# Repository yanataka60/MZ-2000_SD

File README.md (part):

# MZ-80B、MZ-2000、MZ-2200にSD-CARDからのアプリケーション起動、ロード、セーブ機能

　MZ-80B、MZ-2000、MZ-2200でSD-CARDからのアプリケーション起動、BASICなどのアプリケーションからSD-CARDへのロード、セーブを実現するものです。

　MZ-80B、MZ-2000、MZ-2200では「/」キーを押しながら電源を入れる、又は「/」キーを押しながらIPLボタンを押すことでI/Oデバイスとして繋いだROMからプログラムを読み込ませて起動する機能があります。

　この機能を使ってSD-CARDからアプリケーションを起動させる機能を持たせたMONITOR SB-1520(MZ-80B)、MONITOR 1Z-1Z001M(MZ-2000)をROM起動させます。

　SD対応MONITORからはFD又はFDLコマンドでSDからアプリケーションをLOAD実行ができます。

　LOAD実行範囲は、0000h～F7FFhです。アプリケーション、ゲームを起動させるにはほぼ問題ないと思います。

　(2023.1.1)FDコマンドでの読み込み実行で読み込み終了アドレスがF800h以降であっても読み込みスタートアドレスが12A0h以降だった場合に限りFFFFhまでの読み込みに対応しました。

　なお、アプリケーション中でのSD-CARDとのロード、セーブについては、アプリケーションごとにSD-CARD対応化を行う必要があります。

　EXPANSION UNITが接続されていないMZ-2000、MZ-2200でも使えます。

　MZ-2500の80Bモード、2000モードでも使えます。

#### (追記2023.3.8)MZ-2500のZ80PIOとI/Oアドレスがぶつかっていることを失念していました。80Bモード、2000モードでは問題ありませんが、MZ-2500モードではMZ-2000_SDを接続したままRS-232C、マウスは使えません。

　現在、アプリケーション中でのSD-CARDとのLOAD、SAVEに対応できているものは以下のとおりです。

### MZ-2000、MZ-2200用
|アプリケーション名|備考|
| ------------ | ------------ |
|BASIC MZ-1Z001||
|BASIC MZ-1Z002||
|16BIT BASIC 1Z-012||
|MZ-LOGO V1.0||
|MZ-LISP       |I/O '85/3月号|
|S-OS SWORD TAPE版|Oh!MZ '86/2月号|
|TS-2000       |I/O '82/12月号|
|BASE          |I/O '83/1月号|
|WICS          |I/O '83/2月号|
|EDASM         |Oh!MZ '85/1月号|
|TTL           |Oh!MZ '84/10月号|

### MZ-80B用
|アプリケーション名|備考|
| ------------ | ------------ |
|BASIC SB-5520 ||
|MZ-LISP       |I/O '85/3月号|
|FORTRAN       |I/O別冊MZ-80B活用研究|
|S-OS SWORD TAPE版|Oh!MZ '86/2月号|
|TS-1000       |I/O '82/2月号 I/O別冊MZ-80B活用研究|
|WICS          |I/O '82/3月号 I/O別冊MZ-80B活用研究|
|TTL           |Oh!MZ '84/10月号|

　なお、Arduino、ROMへ書き込むための機器が別途必要となります。

## 回路図
　2枚構成のRev2.3(Rev3.3)と1枚構成のRev4.3があります。

　Rev2.3(Rev3.3)は手元にSD-CARDが置ける、拡張ボックスが無くてもMZ-2000に装着が可能です。

　Rev4.3は拡張ボックス専用でSD-CARDが背面にいってしまいますが、すっきりと収納できます。

　好きな方を選択してください。

　注1)MZ-2000_SD(SD-CARD UNIT基板)でU5 GAL22V10をTTLに置き換えたRev3.3基板のKiCadデータを追加しました。後述「MZ-2000_SD(SD-CARD UNIT基板)Rev3.3」を参照してください。

　注2)MZ-80Bに拡張I/Oポートが装備されていない場合の接続方法については後述「MZ-80Bの拡張I/Oポートを使わずに接続する場合」を参照してください。

　KiCadフォルダ内のMZ-2000_EXT-BOARDフォルダのMZ-2000_EXT-BOARD.pdf、MZ2000_SDフォルダのMZ2000_SD.pdfを参照してください。

[インタフェース基板回路図](https://github.com/yanataka60/MZ-2000_SD/blob/main/KiCad/MZ-2000_EXT-BOARD/MZ-2000_EXT-BOARD.pdf)

[SD-CARD UNIT Rev2.3基板回路図](https://github.com/yanataka60/MZ-2000_SD/blob/main/KiCad/MZ-2000_SD/MZ2000_SD.pdf)

## 部品

### MZ-2000_EXT-BOARD(インタフェース基板)
|番号|品名|数量|備考|
| ------------ | ------------ | ------------ | ------------ |
|J2|2x22Pinコネクタ|1|秋月電子通商 PH-2x40SGなど|
|J4|DCジャック|1|秋月電子通商 MJ-179PHなど|
|J5|2x22Pinコネクタ|1|秋月電子通商 PH-2x40RGなど(EXPANSION UNITを使う場合には必要ありません)|
|S1|3Pスライドスイッチ|1|秋月電子通商 SS12D01G4など|

### MZ-2000_SD(SD-CARD UNIT基板)Rev2.3
|番号|品名|数量|備考|
| ------------ | ------------ | ------------ | ------------ |
|J1|2x22Pinコネクタ|1|秋月電子通商 PH-2x40RGなど|
||J2、J3のいずれか|||
|J2|Micro_SD_Card_Kit|1|秋月電子通商 AE-microSD-LLCNV (注1)|
|J3|MicroSD Card Adapter|1|Arduino等に使われる5V電源に対応したもの (注3)|
|U1,U2|74LS273|2||
|U3|8255|1||
|U4|Arduino_Pro_Mini_5V|1|Atmega328版を使用 168版は不可。(注2)|
|U5|GAL22V10|1||
|U6|27256/29C256/27512/27C512相当品|1|27256/29C256を使うときは、S1を5V側にして使うこと。28C256はピン配置が違うので使えません。|
|U9|74LS245|1||
|C1|電解コンデンサ 16v100uF|1||
|C2-C7|積層セラミックコンデンサ 0.1uF|6||
|S1|3Pスライドスイッチ|1|秋月電子通商 SS12D01G4など|
||ピンヘッダ|2Pin分|Arduino_Pro_MiniにはA4、A5用のピンヘッダが付いていないため別途調達が必要です 秋月電子通商 PH-1x40SGなど|
||ピンソケット(任意)|26Pin分|Arduino_Pro_Miniを取り外し可能としたい場合に調達します 秋月電子通商 FHU-1x42SGなど|

　　　注1)秋月電子通商　AE-microSD-LLCNVのJ1ジャンパはショートしてください。

　　　注2)Arduino Pro MiniはA4、A5ピンも使っています。

　　　注3)Arduino等に使われる5V電源に対応したMicroSD Card Adapterも正しく信号を繋げば使えるとご報告いただきました。

### MZ-2000_SD(SD-CARD UNIT基板)Rev3.3
　MZ-2000_SD(SD-CARD UNIT基板)Rev2.3のU5 GAL22V10が以下の部品に置き換わっています。以下の部品以外はMZ-2000_SD(SD-CARD UNIT基板)Rev2.3の説明を参照してください。
|番号|品名|数量|備考|
| ------------ | ------------ | ------------ | ------------ |
|U5 U7|74LS04|2||
|U8 U11|74LS30|2||
|U10|74LS10|1||
|C8-C11|積層セラミックコンデンサ 0.1uF|4||

#### Rev3.3回路図
[SD-CARD UNIT基板Rev3.3回路図](https://github.com/yanataka60/MZ-2000_SD/blob/main/KiCad/MZ-2000_SD_3_3/MZ2000_SD_33.pdf)

### MZ-2000_SD(SD-CARD UNIT基板)Rev4.3
　EXT-BOARDとSD-CARD UNIT基板Rev3.3を1枚の基板とした拡張スロット装着専用の基板となります。

　MZ-2000、MZ-2200ならEXPANSION UNIT、MZ-80Bなら拡張I/Oポート、MZ-2500なら拡張ユニットが必要です。

　MZ-2000_SD(SD-CARD UNIT基板)Rev2.3のU5 GAL22V10がTTLに置き換わっています。

　また、J1はカードエッジになっていますので「2x22Pinコネクタ」は必要なく、EXT-BOARDを必要としないのでフラットケーブルも不要です。

|番号|品名|数量|備考|
| ------------ | ------------ | ------------ | ------------ |
||J5、J6のいずれか|||
|J5|Micro_SD_Card_Kit|1|秋月電子通商 AE-microSD-LLCNV (注1)|
|J6|MicroSD Card Adapter|1|Arduino等に使われる5V電源に対応したもの (注3)|
|U1,U2|74LS04|2||
|U3,U4|74LS30|2||
|U5|74LS10|1||
|U6,U7|74LS273|2||
|U8|74LS245|1||
|U9|27256/29C256/27512/27C512相当品|1|27256/29C256を使うときは、S1を5V側にして使うこと。28C256はピン配置が違うので使えません。|
|U10|8255|1||
|U11|Arduino_Pro_Mini_5V|1|Atmega328版を使用 168版は不可。(注2)|
|C1|電解コンデンサ 16v100uF|1||
|C2-C11|積層セラミックコンデンサ 0.1uF|10||
|S2|3Pスライドスイッチ|1|秋月電子通商 SS12D01G4など|
||ピンヘッダ|2Pin分|Arduino_Pro_MiniにはA4、A5用のピンヘッダが付いていないため別途調達が必要です 秋月電子通商 PH-1x40SGなど|
||ピンソケット(任意)|26Pin分|Arduino_Pro_Miniを取り外し可能としたい場合に調達します 秋月電子通商 FHU-1x42SGなど|

　　　注1)秋月電子通商　AE-microSD-LLCNVのJ1ジャンパはショートしてください。

　　　注2)Arduino Pro MiniはA4、A5ピンも使っています。

　　　注3)Arduino等に使われる5V電源に対応したMicroSD Card Adapterも正しく信号を繋げば使えるとご報告いただきました。

#### Rev4.3回路図
[SD-CARD UNIT基板Rev4.3回路図](https://github.com/yanataka60/MZ-2000_SD/blob/main/KiCad/MZ-2000_SD_4_3/MZ2000_SD_43.pdf)

.JPG)
.JPG)
.JPG)

### MicroSD Card Adapterを使う
J3に取り付けます。

MicroSD Card Adapterについているピンヘッダを除去してハンダ付けするのが一番確実ですが、J3の穴にMicroSD Card Adapterをぴったりと押しつけ、裏から多めにハンダを流し込むことでハンダ付けをする方法もあります。なお、この方法の時にはしっかりハンダ付けが出来たかテスターで導通を確認しておいた方が安心です。

ハンダ付けに自信のない方はJ2の秋月電子通商　AE-microSD-LLCNVをお使いください。AE-microSD-LLCNVならパワーLED、アクセスLEDが付いています。

.JPG)

.JPG)

.JPG)

.JPG)

### その他必要なもの
　基板のコネクタは2x22Pinで設計していますが、2.54mmピッチ2x22Pinフラットケーブルが手に入りにくいので2.54mmピッチ2x25Pinフラットケーブルで代用しています。

　2.54mmピッチ2x22Pinフラットケーブルが手に入るようであればそちらをお使いください。

#### EXPANSION UNITの拡張スロットに挿入して使用する場合
・2.54mmピッチ2x25Pinフラットケーブル

　長さは50～70cmあれば前面まで持ってこられます。

#### EXPANSION UNITを使わない場合
・2.54mmピッチ2x25Pinフラットケーブル、ただし片側はカードエッジコネクタ

　長さは50～70cmあれば全面まで持ってこられます。

・2.54mmピッチ2x25Pinフラットケーブル

　インタフェース基板とSD-CARD UNIT基板は重ねられるので10cm以上の長さがあれば十分です。

## GAL22V10への書込み
　WINCUPLファルダのMZ2000_SD.jedをROMライター(TL866II Plus等)を使ってGAL22V10に書き込んでください。

## ROMへの書込み
　まず、BASICからMONITOR(0000h～129Fh)を抜き出し、バイナリファイルとして保存します。

|機種名|BASIC名|モニタ名|
| ------------ | ------------ | ------------ |
|MZ-80B|SB-5520|SB-1520|
|MZ-2000、MZ-2200|MZ-1Z001 or MZ-1Z002|MZ-1Z001M|

バイナリエディタで以下の修正をします。
### MZ-80B SB-1520
|ADDRESS|修正前|修正後|
| ------------ | ------------ | ------------ |
|0000|C3 3B 00|00 18 38|
|00AE|01 76 49(C3 76 49)|C3 A0 12|
|00F6|56 17 02|46 00 F8|
|0252|16 01 21|C3 03 F8|
|0283|16 02 ED|C3 06 F8|
|028F|16 04 21|C3 09 F8|
|02B3|16 08 ED|C3 0C F8|
|02BF|16 08 ED|C3 0F F8|

### MZ-2000、MZ-2200 MZ-1Z001M
|ADDRESS|修正前|修正後|
| ------------ | ------------ | ------------ |
|0000|C3 3B 00|00 18 38|
|00AE|01 05 4C(C3 05 4C)|C3 A0 12|
|00E5|56      |46      |
|00E7|17 02   |00 F8   |
|0252|16 01 21|C3 03 F8|
|0283|16 02 ED|C3 06 F8|
|028F|16 04 21|C3 09 F8|
|02B3|16 08 ED|C3 0C F8|
|02BF|16 08 ED|C3 0F F8|

　次にEXT-ROMフォルダ内のEXT-ROM_SD MZ-80B.bin又はEXT-ROM_SD MZ-2000.binをMONITORの後ろ(12A0h～)に付け加えて保存します。出来上がるバイナリファイルは0000h～198Ehとなるはずです。

　出来上がったバイナリファイルをROMライター(TL866II Plus等)を使って27C256に書き込んでください。

　27C512を使えば二つのバイナリファイルを切り替えて使うような使い方ができます。このとき、一つのバイナリファイルは32KByte、二つ合わせて64KByteにして書き込んでください。

### 参考)起動プロセス
　1　「/」キーを押しながら電源を入れる、又は「/」キーを押しながらIPLボタンを押す。

　2　EXT-ROMからプログラムが読み込まれ、ノーマル時のメモリマップに切り替わった後、リセットされる。

　3　MINITORが起動し、MZの初期化が行われた後、12A0hにJUMPする。

　4　12A0hからの転送プログラムにより、SDアクセスルーチンをF800h以降に転送する。

　5　MZ-2000_SDの8255を初期化する。

　6　12A0hからの転送プログラムが再度起動しないよう00AEhに01hを書き込む。

　7　コマンドプロンプトに戻る。

　8　FDコマンド又はFDLコマンドによりSD-CARD内アプリケーションのLOAD実行が指示されるとF800hのSDアクセスルーチンにJUMPする。

　9　指定したファイルがSDに存在したらスタックポインタをFFFFhに設定する。

　10　MZTファイルのヘッダ情報にあるLOAD開始アドレスからファイル長分をSD-CARDから読み出しメインメモリに書き込む。

　　　この時、LOAD終了アドレスがF800h以降でLOAD開始アドレスが12A0h以降ならSD-LOADルーチンを1200h～124Fhにコピーし1206hにJUMPしてLOADを実行する。

　11　実行開始アドレスが0000hでないならスタックポインタを1140hに設定する。

　12　実行開始アドレスにJUMPする。

### ROMにBOOT LOADERを書き込む方式の追加
　前述のBASICからMONITORを抜き出してROMに書き込む方式は、自分が所有しているBASICから抜き出してROMに書き込むには問題が無いのですが、書き込み済みROMの配布はSHARPの著作権があるので出来ません。

　そこで「@BOOT-A MZ-2000.bin」、「@BOOT-A MZ-80B.bin」というバイナリファイルをSD-CARDから読み込み起動するプログラムをROMに書き込む方式を追加しました。

　ROMに27256を使えば「@BOOT-A MZ-xxxx.bin」、27512を使えば「@BOOT-A MZ-xxxx.bin」と「@BOOT-B MZ-xxxx.bin」を切り替えて読み込むことができます。

　前述「ROMへの書込み」の手順により修正を加えたMONITORの後ろ(12A0h～)にEXT-ROM_SD MZ-2000.bin又はEXT-ROM_SD MZ-80B.binを付け加えて保存したバイナリファイル(従来ROMに書き込んでいたバイナリファイル)を「@BOOT-A MZ-2000.bin」又は「@BOOT-A MZ-80B.bin」のファイルネームでSD-CARDに保存してください。

　27512を使うのであれば同様にBASICを加工したバイナリファイル(従来ROMに書き込んでいたバイナリファイル)を「@BOOT-B MZ-2000.bin」又は「@BOOT-B MZ-80B.bin」のファイルネームでSD-CARDに保存することでスイッチの切り替えで読み込むことができます。

#### BOOT LOADERをROMに書き込む
　BOOT_LOADERフォルダにある「BOOT_A_LOADER.bin」または「BOOT_AB_LOADER.bin」をROMに書き込みます。

　　27256を使用する場合は「BOOT_A_LOADER.bin」を書き込んでください。

　　27512を使用する場合は「BOOT_AB_LOADER.bin」を書き込んでください。

#### 「@BOOT-A MZ-xxxx.bin」を作成してSD-CARDに保存する
　「ROMへの書込み」を参照してバイナリファイル(従来ROMに書き込んでいたバイナリファイル)を作成します。

　出来上がったファイルの名前は、MZ-2000用なら「@BOOT-A MZ-2000.bin」、MZ-80B用なら「@BOOT-A MZ-80B.bin」としてSD-CARDに保存します。

　起動させた機械がMZ-2000か、MZ-80Bか自動的に判断して「@BOOT-A MZ-2000.bin」、「@BOOT-A MZ-80B.bin」のどちらかを読み込まれます。

#### 「@BOOT-B MZ-xxxx.bin」を作成してSD-CARDに保存する(27512を使用する場合)
　後述の「BASICをEXT-ROMから起動させる」を参照してバイナリファイル(従来ROMに書き込んでいたバイナリファイル)を作成し、出来上がったファイルの名前をMZ-2000用なら「@BOOT-B MZ-2000.bin」、MZ-80B用なら「@BOOT-B MZ-80B.bin」としてSD-CARDに保存します。

　起動させた機械がMZ-2000か、MZ-80Bか自動的に判断して「@BOOT-B MZ-2000.bin」、「@BOOT-B MZ-80B.bin」のどちらかを読み込まれます。

#### Arduinoプログラム
　この機能に対応させるためArduinoプログラムも更新しました。この機能を使いたい場合にはArduinoプログラムも書き込み直してください。

## Arduinoプログラム

　MZ-80K_SDと全く同じものを使用しています。

　MZ-80K_SDでソケットを使用して差込式にしているのであればそのままMZ-2000_SDに差して使えます。

　Arduino IDEを使ってMZ-80Kリポジトリ Arduinoフォルダ内のMZ-80K_SD.inoを書き込みます。

　SdFatライブラリを使用しているのでArduino IDEメニューのライブラリの管理からライブラリマネージャを立ち上げて「SdFat」をインストールしてください。

　「SdFat」で検索すれば見つかります。「SdFat」と「SdFat - Adafruit Fork」が見つかりますが「SdFat」のほうを使っています。

注)Arduinoを基板に直付けしている場合、Arduinoプログラムを書き込むときは、MZ-2000本体とは接続を外し、74LS04を外したうえで書き込んでください。

## 接続
### MZ-80B、MZ-2000、MZ-2200、MZ-2500の拡張スロットに差し込む
　インタフェース基板は、安価に発注するために10cmx10cmで設計しているのでMZ-80B、MZ-2000、MZ-2200の拡張カードとしては寸足らずです。右側をガイドスロットに沿って差し込めるように設計しています。

#### 2025.7.14追記) カードエッジコネクタは規格通りです。左側をガイドスロットに沿って差し込むと違うピンが接触してしまうわけではありません。(左側をガイドスロットに沿って差し込もうとしても差し込めません)

　インタフェース基板からMZ-2000_SDへのフラットケーブルは真ん中のJ2に差してください。

### MZ-2200、MZ-80B、MZ-2500拡張スロットへの抜き差しに苦労する場合
　MZ-2200 EXPANSION UNITにインタフェース基板を挿入しようとしたところ、抜き差しが非常に硬く苦労する個体がありました。

　開発ではMZ-2000 EXPANSION UNITでのスムーズな抜き差しを確認していますが、抜き差しに苦労する場合には画像の部分をほんの少しヤスリ掛け(4～5回)するだけでかなりスムーズになりますのでお試しください。

### MZ-2000、MZ-2200のEXPANSION UNITを使わずに接続する場合
　インタフェース基板のカードエッジ反対側のJ5と本体のカードエッジを接続します。

　インタフェース基板からMZ-2000_SDへのフラットケーブルは真ん中のJ2に差してください。

#### カードエッジコネクタを使う
　変則的ではありますが、インタフェース基板に基板用カードエッジコネクタのピンを曲げて付けてみました。

　カードエッジコネクタを基板にハンダ付けすると上面、下面が逆になってしまいますのでカードエッジコネクタは基板の裏面に付ける必要があります。

　カードエッジコネクタB列のピンは90度曲げることでそのままハンダ付けできますが、A列のピンは空中に浮いてしまいますので手配線する必要があります。

　また、MZ-2000本体のカードエッジに挿す時には、基板を逆さまに挿しますのでフラットケーブルが邪魔になって結構斜めになっています。

　ちょっと強引な付け方になりますので試される方は自己責任でお願いします。

### MZ-80Bの拡張I/Oポートを使わずに接続する場合
　MZ-80Bに拡張I/Oポートが装備されていない場合には、MZ-80B用のインタフェース基板を使用します。

[MZ-80Bインタフェース基板回路図](https://github.com/yanataka60/MZ-2000_SD/blob/main/KiCad/MZ-80B_EXT-BOARD/mz-80b.pdf)

|番号|品名|数量|備考|
| ------------ | ------------ | ------------ | ------------ |
|J2|2x22Pinコネクタ|1|秋月電子通商 PH-2x40SGなど|
|J3|1Pinコネクタ|1|秋月電子通商 FHU-1x42SGなど|
|J4|DCジャック|1|秋月電子通商 MJ-179PHなど(J3により5Vを供給すれば特に必要はありません)|
|J5|2x20Pinソケット|1|秋月電子通商 FHU-2x42SGなど|
|S1|3Pスライドスイッチ|1|秋月電子通商 SS12D01G4など(J3により5Vを供給すれば特に必要はありません)|
||2.54mmピッチ2x25Pinフラットケーブル|1|長さは50～70cm(手に入れば2x22Pin)|

J5の2x20Pinソケットは基板裏側にハンダ付けします。

ケーブルはMZ-80Bインターフェース基板のJ3から一回反転させてMZ-8000_SDに繋ぎます。

.JPG)

MZ-80B本体後ろからカバーを開け、メインボードに二つ並んでいる2x20Pinコネクタのうち手前の2x20PinコネクタにMZ-80Bインターフェース基板を挿し込みます。ピンの位置を確認してずれて挿すことのないように装着します。

.JPG)

MZ-80B本体内部の拡張I/Oポート用電源から5V電源を供給すれば扱いが楽です。

.JPG)

.JPG)

.JPG)

MZ-80B用拡張I/Oポートが手に入ったときにはMZ-80Bインタフェース基板のカードエッジ側を拡張I/Oポートに挿してください。

.JPG)

### MZ-2500の拡張ユニットが無く、本体内部のコネクタに接続する場合
#### 2023.7.23追記 MZ-2500本体内部のコネクタに変換アダプタを挿し込む方法では正常に動作しない場合があるようです。正常に動作しない場合には、後述の変換アダプタをMZ-2000_SD基板側に装着する方法を試してください。
　MZ-2000_SDと本体内部のコネクタを単純にPinケーブルで接続するとA、B面が逆転してしまうため動作しません。MZ-2000_SDのコネクタを裏面にハンダ付けするか、変換アダプタを自作して接続してください。

　変換アダプタは、MZ-2000 EXT-BOARDか、MZ-80B EXT-BOARDのどちらかで自作できます。

　EXT-BOARD基板の長さではケースにあたってしまうので若干カットします。

　カードエッジ部を挟み込むように25x2PinピンソケットをEXT-BOARD基板の表面からみて左側に3x2Pinがはみ出すようにハンダ付けします。

　EXT-BOARD基板の裏面に22x2Pinピンヘッダをつけて出来上がりです。

#### 作成した変換アダプタをMZ-2000_SD基板側に取り付ける場合
　MZ-2500本体内部のコネクタに変換アダプタを挿し込む方法で動作しない場合には、作成した変換アダプタをMZ-2000_SD基板側に取り付ける方法を試してみてください。

　信号的には同じ接続のはずですが、コネクタの挿し込み具合等により前述の方法では動作しない場合があるようです。

## 外部電源
　EXPANSION UNITを使わずにMZ-2000、MZ-2200本体に接続する場合は、本体側カードエッジには5Vが出ていないため、外部電源が必要となります。

　なお、MZ-2000_SD程度の消費電流であればMZ-2000本体内部から供給しても問題ないと思います。挑戦される方は自己責任でお願いします。

　拡張スロットに差す場合には外部電源は必要ありません。拡張スロットに差した状態で外部電源を供給すると故障の原因となる恐れがあります。拡張スロットに差す運用のみであればインタフェース基板にはDCジャック及びJ5ピンヘッダは取り付けないほうが無難です。
## SD-CARD
　出来れば8GB以下のSDカードを用意してください。

　ArduinoのSdFatライブラリは、SD規格(最大2GB)、SDHC規格(2GB～32GB)に対応していますが、SDXC規格(32GB～2TB)には対応していません。

　また、SDHC規格のSDカードであっても32GB、16GBは相性により動作しないものがあるようです。

　FAT16又はFAT32が認識できます。NTFSは認識できません。

　ルートに置かれたMZTファイルのみ認識できます。(MZT以外のファイル、フォルダも表示されますがLOAD実行の対象になりません)

　ファイル名は「.MZT」を除いて32文字まで、ただし半角カタカナ、及び一部の記号はArduinoが認識しないので使えません。パソコンでファイル名を付けるときはアルファベット、数字および空白でファイル名をつけてください。

## 操作方法
　ROM起動させた場合にMONITORコマンド入力待ちから以下のコマンドが拡張されます。

　MONITOR本来のMコマンド、Dコマンド、Jコマンドは同じように使えます。

　Lコマンド、SコマンドはSD-CARD対応として使えます。LコマンドでのLOAD実行範囲は12A0h～F7FFhです。

　Vコマンドは、使えません。

　以下、SD-CARD内のファイルに付けられるファイル名をDOSファイル名、MZT形式ファイルのインフォメーションブロック内ファイル名をIBFファイル名とします。

### FD[CR]
　FDのみでDOSファイル名「0000.MZT」がLOAD及び実行されます。

　「0000.MZT」は、パソコンでBASIC等をリネームコピーして作成してください。

　LOAD実行可能範囲は0000h～F7FFhです。

　注)読み込み終了アドレスがF800h以降であっても読み込みスタートアドレスが12A0h以降だった場合に限りFFFFhまで読み込めます。

### FD　DOSファイル名[CR]
　DOSファイル名で指定したバイナリファイルをLOADして実行します。

　「.MZT」は省略可能です。

　LOAD実行可能範囲は0000h～F7FFhです。

例)

FD　TEST[CR]

　注)読み込み終了アドレスがF800h以降であっても読み込みスタートアドレスが12A0h以降だった場合に限りFFFFhまで読み込めます。

### FDL[CR]
　SD-CARDルートディレクトリにあるファイルの一覧を表示します。20件表示したところで指示待ちになるので打ち切るならSHIFT+BREAK又は↑を入力すると打ち切られ、Bキーで前の20件に戻ります。それ以外のキーで次の20件を表示します。

　行頭に「*FD」を付加して表示してあるので実行したいファイルにカーソルキーを合わせて[CR]キーを押すだけでLOAD、実行が可能です。

　表示される順番は、登録順となりファイル名アルファベッド順などのソートした順で表示することはできません。

　LOAD実行可能範囲は0000h～F7FFhです。

### FDL　x[CR]
ファイル名がxで始まるファイルの一覧を表示します。20件表示したところで指示待ちになるので打ち切るならSHIFT+BREAK又は↑を入力すると打ち切られ、Bキーで前の20件に戻ります。それ以外のキーで次の20件を表示します。

xはMZのキーボードから入力可能な32文字までの文字列です。(数字、記号、アルファベット)

　LOAD実行可能範囲は0000h～F7FFhです。

例)

FDL S[CR]

FDL SP[CR]

FDL BASIC S[CR]

### アプリケーションからのLOAD
　L、LOAD等アプリケーションが指定したコマンドの後ろにはIBFファイル名を指定可となっていますが、指定せずにL、LOAD等のコマンドのみで[CR]キーを押します。

　CMTの場合にはここでPLAYボタンを押すよう指示が出るところですが、「DOS FILE:」と表示して行入力待ちになっているのでDOSファイル名を入力して[CR]キーを押します。この時、「.MZT」の入力は省略できます。

　DOSファイル名は「.MZT」を除いて32文字まで、ただし半角カタカナ、及び一部の記号はArduinoが認識しないので使えません。パソコンでファイル名を付けるときはアルファベット、数字および空白でファイル名をつけてください。

例)BASIC MZ-1Z001では

× LOAD "TEST"[CR]

○ LOAD[CR]

　DOS FILE:TEST[CR]

○ LOAD[CR]

　DOS FILE:TEST.MZT[CR]

** 参考 **

　S-OS SWORDでの運用に当たっては起動直後に「DV S:」としてデバイスを各SYSTEMデバイスとしてください。

　FUZZY BASICだけかもしれませんが共通フォーマットデバイスのままだとLOADコマンドでIBFファイル名の省略ができませんでした。

#### LOAD時の特殊コマンド
　「DOS FILE:」と表示して行入力待ちになったときに以下の特殊コマンドが使用可能です。

##### *FDL[CR]
##### *FDL x[CR]
　MONITORコマンド入力待ちからのFDL、FDL xと全く同等のファイル一覧機能が使えます。

　検索結果の行頭には「DOS FILE:」を付加して表示してあるのでLOADしたいファイルにカーソルキーを合わせて[CR]キーを押すだけでLOADが可能です。

　「*FDL」で検索、カーソルで選んで読み込もうとした場合に「DOS FILE:」に戻ってしまうアプリケーションがありますが、再度カーソルを合わせて[CR]すれば読み込めます。

### アプリケーションからのSAVE
　CMTの時と同様にアプリケーションの指定する入力方法、ルールでファイル名等を入力して保存してください。

　ただし、半角カタカナはArduinoが認識できないため、使用できません。アルファベット、数字および空白で指定してください。

　SAVE時は、入力したファイル名がIBFファイル名、DOSファイル名の両方に適用されます。

　DOSファイル名としての「.MZT」は自動的に付加されます。

例)BASIC MZ-1Z001では

○ SAVE "TEST"[CR]

## 操作上の注意
　~~「SD-CARD INITIALIZE ERROR」と表示されたときは、SD-CARDをいったん抜き再挿入したうえでArduinoをリセットしてください。~~

　~~SD-CARDにアクセスしていない時に電源が入ったままで SD-CARDを抜いた後、再挿入しSD-CARDにアクセスすると「SD-CARD INITIALIZE ERROR」となる場合があります。再挿入した場合にはSD-CARDにアクセスする前にArduinoを必ずリセットしてください。~~

　~~SD-CARDの抜き差しは電源を切った状態で行うほうがより確実です。~~

　(2024.3.10) SD-CARDにアクセスしていない時に電源が入ったままでSD-CARDを抜くと再度SD-CARDを挿入してもSD-CARDにアクセスできない問題を解消しました。(Arduinoを最新版に書き換えてください)

　再度SD-CARDを挿入した後、FDL、LOAD、SAVE等でSD-CARDに3回ほどアクセスすれば復旧します。

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
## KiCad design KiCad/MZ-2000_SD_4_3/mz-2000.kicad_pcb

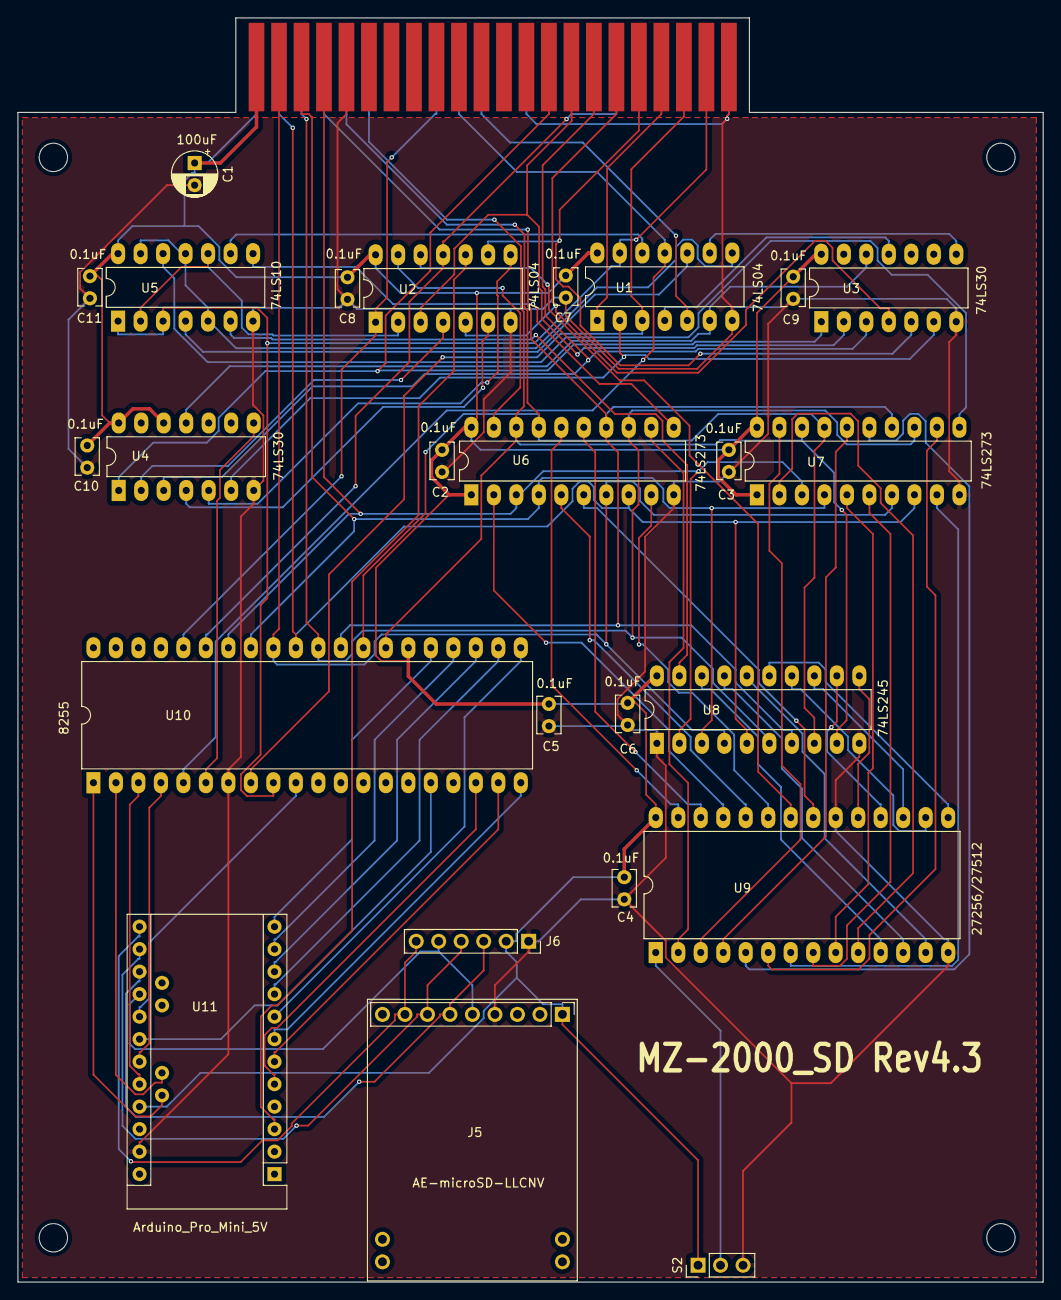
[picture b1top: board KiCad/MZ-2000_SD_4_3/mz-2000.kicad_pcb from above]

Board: 2 copper layers, 115.8 x 142.7 mm, 30 parts (0 on the bottom side), 82 nets.

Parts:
C1: 100uF; CP_Radial_D5.0mm_P2.50mm
C2, C3, C4, C5, C6, C7, C8, C9, C10, C11: 0.1uF; C_Rect_L4.0mm_W2.5mm_P2.50mm
J1: Conn_02x22_Row_Letter_First; BUS_MZ2000
J5: Micro_SD_Card_Kit; AE-microSD-LLCNV
J6: MicroSD Card Adapter; PinSocket_1x06_P2.54mm_Vertical
MH1, MH2, MH3, MH4: MountingHole_3.2mm_M3
S2: SLIDE_SWITCH_3P; PinHeader_1x03_P2.54mm_Vertical
U1, U2: 74LS04; DIP-14_W7.62mm_LongPads
U3, U4: 74LS30; DIP-14_W7.62mm_LongPads
U5: 74LS10; DIP-14_W7.62mm_LongPads
U6, U7: 74LS273; DIP-20_W7.62mm_LongPads
U8: 74LS245; DIP-20_W7.62mm_LongPads
U9: 29C256/27C512; DIP-28_W15.24mm_LongPads
U10: 8255; DIP-40_W15.24mm_LongPads
U11: Arduino_Pro_Mini_5V; Arduino_Pro_Mini

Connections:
+5V: C1.1, C2.1, C3.1, C4.1, C5.1, C6.1, C7.1, C8.1, C9.1, C10.1, C11.1, J1.a1, J1.b1, J5.1, J6.2, S2.1, U1.14, U2.14, U3.14, U4.12, U4.14, U5.14, U6.1, U6.20, U7.1, U7.20, U8.20, U9.28, U10.26, U11.21
/A0: J1.a21, U1.13, U5.1, U5.3, U10.9
/A1: J1.a20, U1.3, U10.8
/A2: J1.a19, U1.1
/A3: J1.a18, U2.9, U3.5
/A4: J1.a17, U2.5, U3.4
/A5: J1.a16, U3.3, U4.3
/A6: J1.a15, U2.3, U3.2
/A7: J1.a14, U3.1, U4.1
/CS: J5.8, J6.6, U11.13
/D0: J1.a4, U6.3, U7.3, U8.2, U10.34
/D1: J1.a3, U6.4, U7.4, U8.3, U10.33
/D2: J1.a2, U6.7, U7.7, U8.4, U10.32
/D3: J1.b2, U6.8, U7.8, U8.5, U10.31
/D4: J1.b3, U6.13, U7.13, U8.6, U10.30
/D5: J1.b4, U6.14, U7.14, U8.7, U10.29
/D6: J1.b5, U6.17, U7.17, U8.8, U10.28
/D7: J1.b6, U6.18, U7.18, U8.9, U10.27
/MISO: J5.6, J6.3, U11.15
/MOSI: J5.7, J6.4, U11.14
/RESET: J1.b17, U2.11, U10.35
/SCK: J5.5, J6.5, U11.16
/~IOREQ: J1.b11, U1.5
/~RD: J1.b10, U1.11, U10.5
/~WR: J1.b9, U2.1, U10.36
GND: C1.2, C2.2, C3.2, C4.2, C5.2, C6.2, C7.2, C8.2, C9.2, C10.2, C11.2, J1.a5, J1.a22, J1.b13, J1.b22, J5.4, J6.1, S2.3, U1.7, U2.7, U3.7, U4.7, U5.7, U6.10, U7.10, U8.1, U8.10, U9.14, U9.20, U10.7, U11.23
unnamed: S2.2, U9.1
unnamed: U1.2, U3.6, U4.6
unnamed: U1.4, U3.11
unnamed: U1.6, U3.12, U4.11
unnamed: U1.8, U5.5, U5.11, U5.13
unnamed: U1.9, U3.8
unnamed: U1.10, U5.4
unnamed: U1.12, U5.9
unnamed: U2.2, U5.2, U5.10
unnamed: U2.4, U4.2
unnamed: U2.6, U4.4
unnamed: U2.8, U4.5
unnamed: U2.12, U9.22
unnamed: U2.13, U6.19
unnamed: U5.6, U8.19
unnamed: U5.8, U6.11
unnamed: U5.12, U7.11
unnamed: U6.2, U9.25
unnamed: U6.5, U9.24
unnamed: U6.6, U9.21
unnamed: U6.9, U9.23
unnamed: U6.12, U9.2
unnamed: U6.15, U9.26
unnamed: U6.16, U9.27
unnamed: U7.2, U9.10
unnamed: U7.5, U9.9
unnamed: U7.6, U9.8
unnamed: U7.9, U9.7
unnamed: U7.12, U9.6
unnamed: U7.15, U9.5
unnamed: U7.16, U9.4
unnamed: U7.19, U9.3
unnamed: U8.11, U9.19
unnamed: U8.12, U9.18
unnamed: U8.13, U9.17
unnamed: U8.14, U9.16
unnamed: U8.15, U9.15
unnamed: U8.16, U9.13
unnamed: U8.17, U9.12
unnamed: U8.18, U9.11
unnamed: U10.1, U11.A5
unnamed: U10.2, U11.A4
unnamed: U10.3, U11.20
unnamed: U10.4, U11.19
unnamed: U4.8, U10.6
unnamed: U10.10, U11.17
unnamed: U10.16, U11.18
unnamed: U10.18, U11.5
unnamed: U10.19, U11.6
unnamed: U10.20, U11.7
unnamed: U10.21, U11.8
unnamed: U10.22, U11.9
unnamed: U10.23, U11.10
unnamed: U10.24, U11.11
unnamed: U10.25, U11.12
unnamed: U2.10, U11.3

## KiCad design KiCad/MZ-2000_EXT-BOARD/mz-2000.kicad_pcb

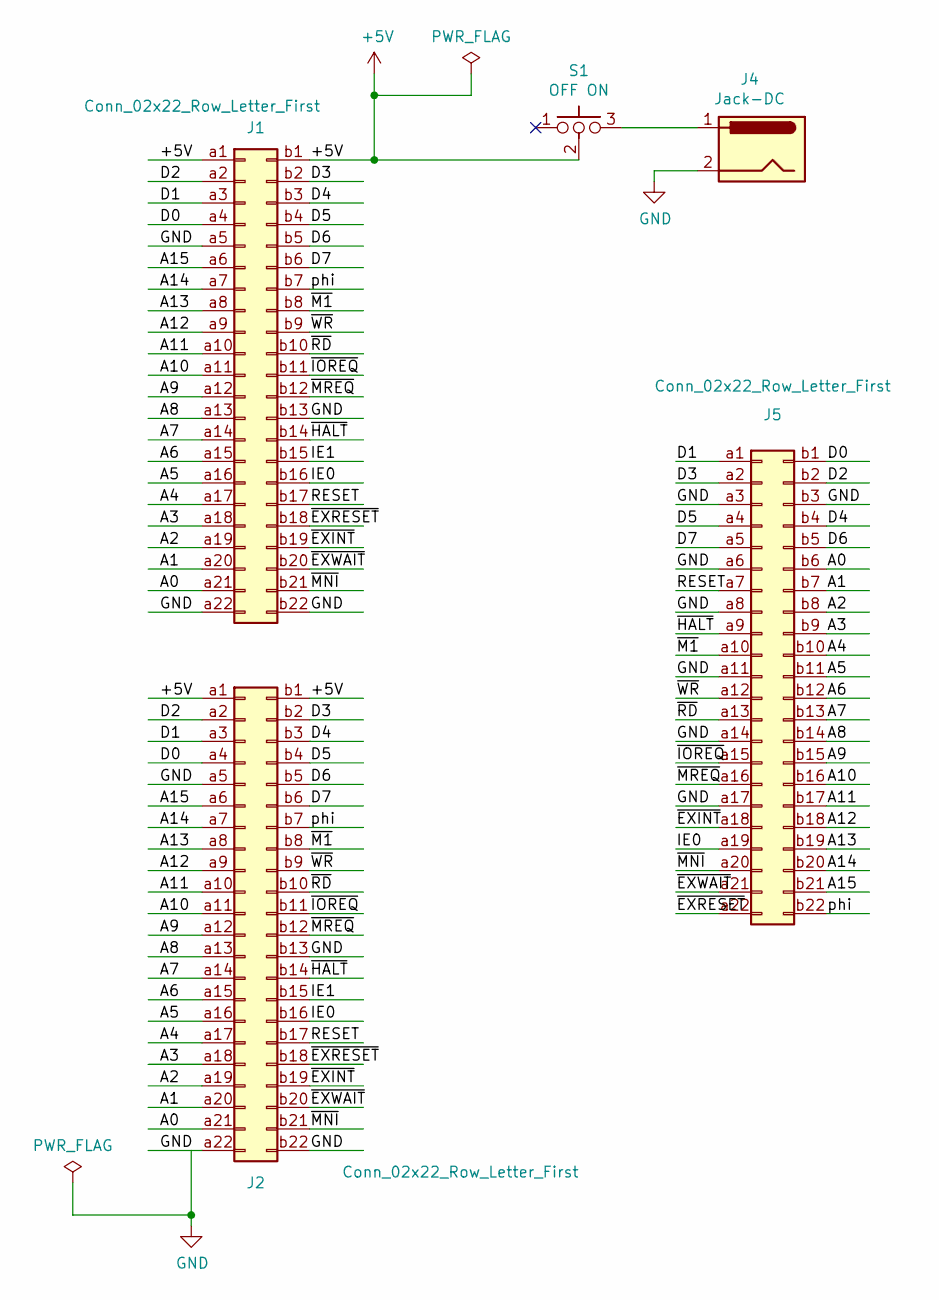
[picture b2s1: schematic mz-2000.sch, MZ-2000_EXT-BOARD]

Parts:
J1: Conn_02x22_Row_Letter_First; BUS_MZ2000
J2, J5: Conn_02x22_Row_Letter_First; PinHeader_2x22_P2.54mm_Vertical
J4: Jack-DC; BarrelJack_Horizontal
S1: OFF ON; PinHeader_1x03_P2.54mm_Vertical

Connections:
+5V: J1.a1, J1.b1, J2.a1, J2.b1, S1.2
/A0: J1.a21, J2.a21, J5.b6
/A1: J1.a20, J2.a20, J5.b7
/A2: J1.a19, J2.a19, J5.b8
/A3: J1.a18, J2.a18, J5.b9
/A4: J1.a17, J2.a17, J5.b10
/A5: J1.a16, J2.a16, J5.b11
/A6: J1.a15, J2.a15, J5.b12
/A7: J1.a14, J2.a14, J5.b13
/A8: J1.a13, J2.a13, J5.b14
/A9: J1.a12, J2.a12, J5.b15
/A10: J1.a11, J2.a11, J5.b16
/A11: J1.a10, J2.a10, J5.b17
/A12: J1.a9, J2.a9, J5.b18
/A13: J1.a8, J2.a8, J5.b19
/A14: J1.a7, J2.a7, J5.b20
/A15: J1.a6, J2.a6, J5.b21
/D0: J1.a4, J2.a4, J5.b1
/D1: J1.a3, J2.a3, J5.a1
/D2: J1.a2, J2.a2, J5.b2
/D3: J1.b2, J2.b2, J5.a2
/D4: J1.b3, J2.b3, J5.b4
/D5: J1.b4, J2.b4, J5.a4
/D6: J1.b5, J2.b5, J5.b5
/D7: J1.b6, J2.b6, J5.a5
/IE0: J1.b16, J2.b16, J5.a19
/IE1: J1.b15, J2.b15
/RESET: J1.b17, J2.b17, J5.a7
/phi: J1.b7, J2.b7, J5.b22
/~EXINT: J1.b19, J2.b19, J5.a18
/~EXRESET: J1.b18, J2.b18, J5.a22
/~EXWAIT: J1.b20, J2.b20, J5.a21
/~HALT: J1.b14, J2.b14, J5.a9
/~IOREQ: J1.b11, J2.b11, J5.a15
/~M1: J1.b8, J2.b8, J5.a10
/~MNI: J1.b21, J2.b21, J5.a20
/~MREQ: J1.b12, J2.b12, J5.a16
/~RD: J1.b10, J2.b10, J5.a13
/~WR: J1.b9, J2.b9, J5.a12
GND: J1.a5, J1.a22, J1.b13, J1.b22, J2.a5, J2.a22, J2.b13, J2.b22, J4.2, J5.a3, J5.a6, J5.a8, J5.a11, J5.a14, J5.a17, J5.b3
unnamed: J4.1, S1.3

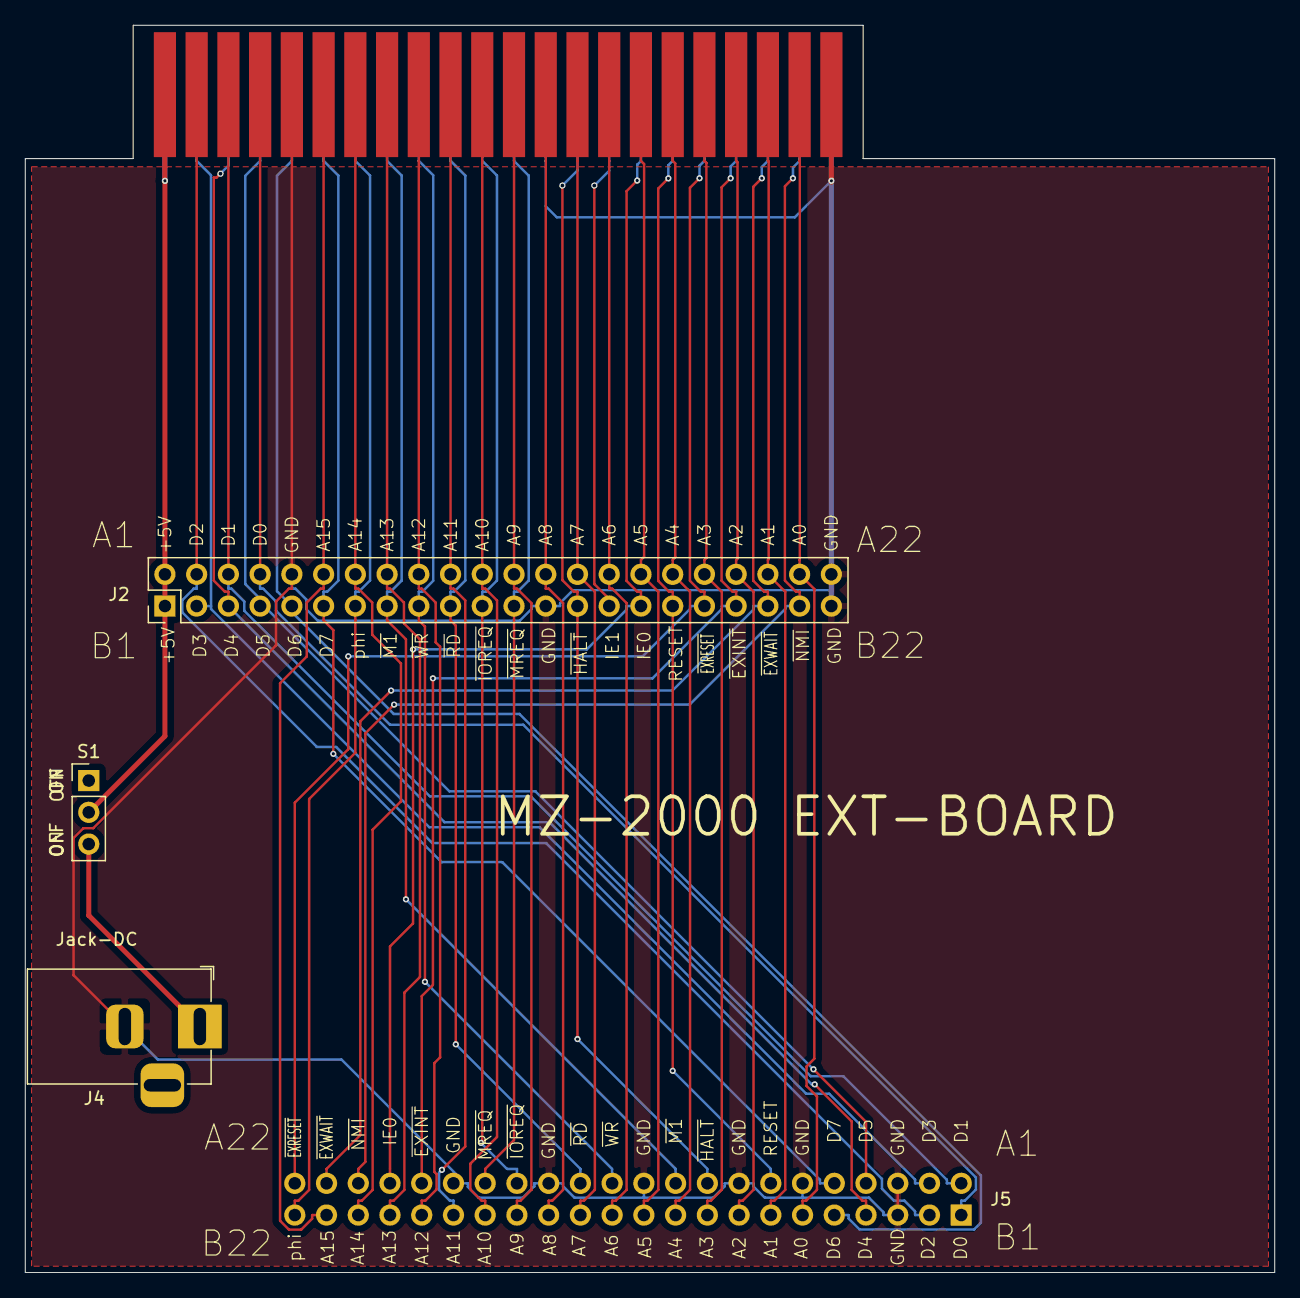
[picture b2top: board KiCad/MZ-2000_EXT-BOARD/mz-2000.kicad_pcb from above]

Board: 2 copper layers, 100.0 x 99.8 mm, 5 parts (1 on the bottom side), 41 nets.

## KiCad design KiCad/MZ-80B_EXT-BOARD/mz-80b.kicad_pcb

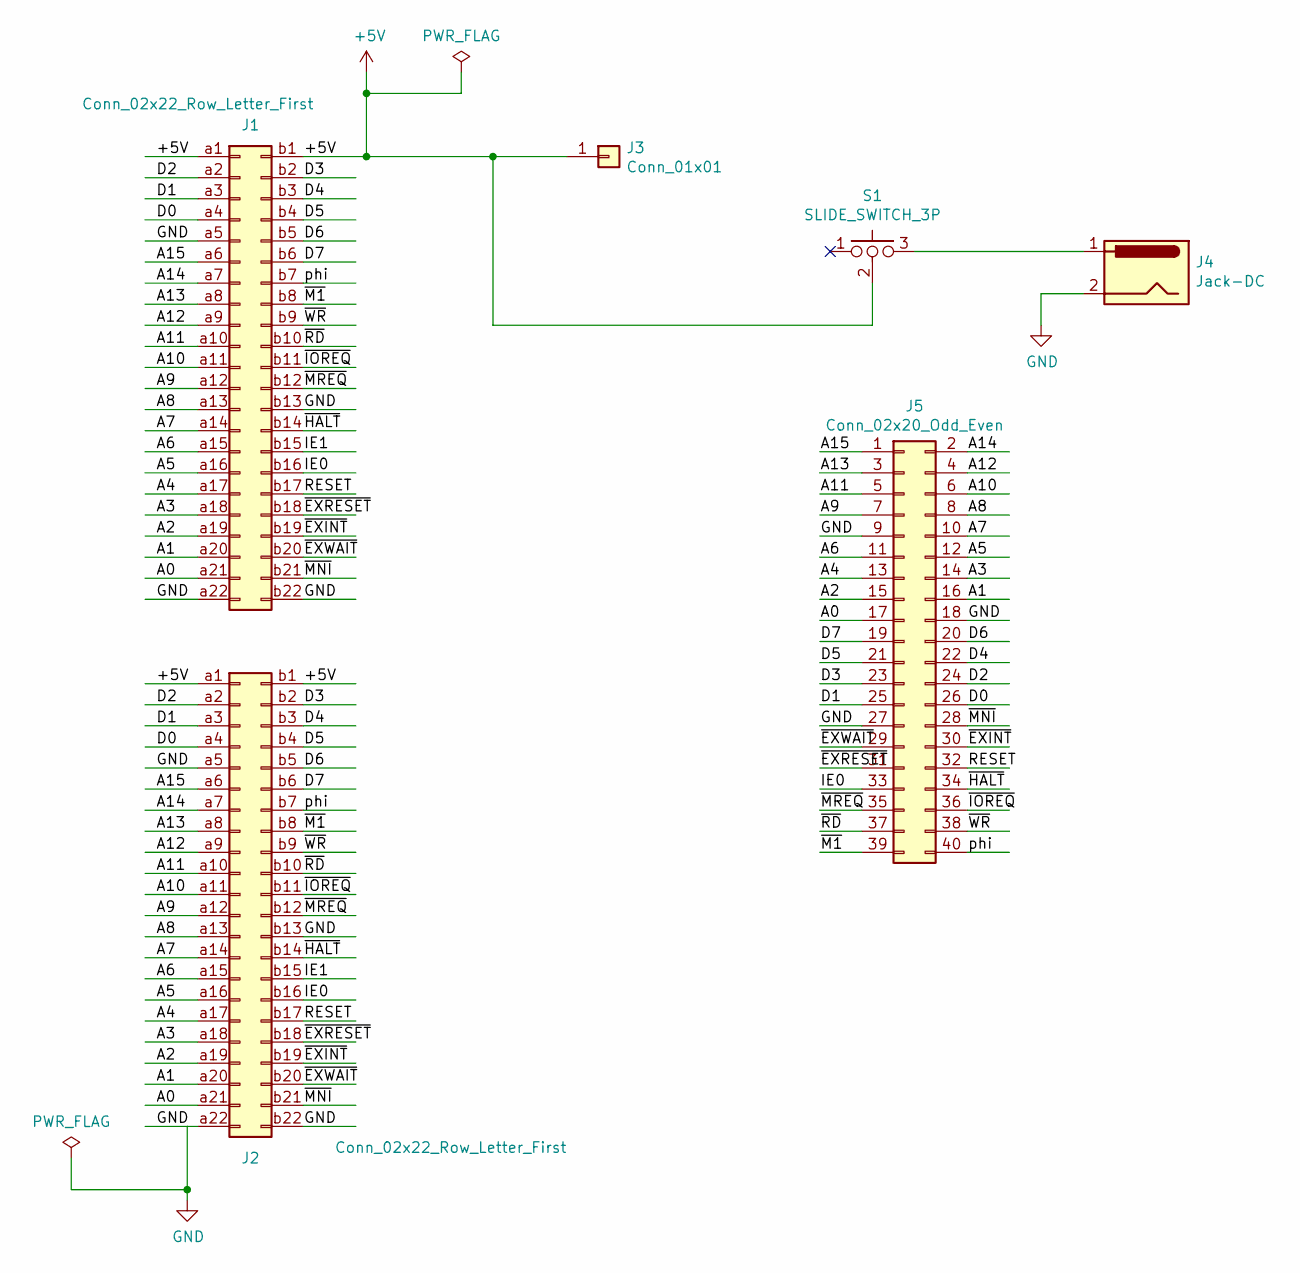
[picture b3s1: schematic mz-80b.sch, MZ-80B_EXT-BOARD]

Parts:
J1: Conn_02x22_Row_Letter_First; BUS_MZ2000
J2: Conn_02x22_Row_Letter_First; PinHeader_2x22_P2.54mm_Vertical
J3: Conn_01x01; PinHeader_1x01_P2.54mm_Vertical
J4: Jack-DC; BarrelJack_Horizontal
J5: Conn_02x20_Odd_Even; PinHeader_2x20_P2.54mm_Vertical
S1: SLIDE_SWITCH_3P; PinHeader_1x03_P2.54mm_Vertical

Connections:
+5V: J1.a1, J1.b1, J2.a1, J2.b1, J3.1, S1.2
/A0: J1.a21, J2.a21, J5.17
/A1: J1.a20, J2.a20, J5.16
/A2: J1.a19, J2.a19, J5.15
/A3: J1.a18, J2.a18, J5.14
/A4: J1.a17, J2.a17, J5.13
/A5: J1.a16, J2.a16, J5.12
/A6: J1.a15, J2.a15, J5.11
/A7: J1.a14, J2.a14, J5.10
/A8: J1.a13, J2.a13, J5.8
/A9: J1.a12, J2.a12, J5.7
/A10: J1.a11, J2.a11, J5.6
/A11: J1.a10, J2.a10, J5.5
/A12: J1.a9, J2.a9, J5.4
/A13: J1.a8, J2.a8, J5.3
/A14: J1.a7, J2.a7, J5.2
/A15: J1.a6, J2.a6, J5.1
/D0: J1.a4, J2.a4, J5.26
/D1: J1.a3, J2.a3, J5.25
/D2: J1.a2, J2.a2, J5.24
/D3: J1.b2, J2.b2, J5.23
/D4: J1.b3, J2.b3, J5.22
/D5: J1.b4, J2.b4, J5.21
/D6: J1.b5, J2.b5, J5.20
/D7: J1.b6, J2.b6, J5.19
/IE0: J1.b16, J2.b16, J5.33
/IE1: J1.b15, J2.b15
/RESET: J1.b17, J2.b17, J5.32
/phi: J1.b7, J2.b7, J5.40
/~EXINT: J1.b19, J2.b19, J5.30
/~EXRESET: J1.b18, J2.b18, J5.31
/~EXWAIT: J1.b20, J2.b20, J5.29
/~HALT: J1.b14, J2.b14, J5.34
/~IOREQ: J1.b11, J2.b11, J5.36
/~M1: J1.b8, J2.b8, J5.39
/~MNI: J1.b21, J2.b21, J5.28
/~MREQ: J1.b12, J2.b12, J5.35
/~RD: J1.b10, J2.b10, J5.37
/~WR: J1.b9, J2.b9, J5.38
GND: J1.a5, J1.a22, J1.b13, J1.b22, J2.a5, J2.a22, J2.b13, J2.b22, J4.2, J5.9, J5.18, J5.27
unnamed: J4.1, S1.3

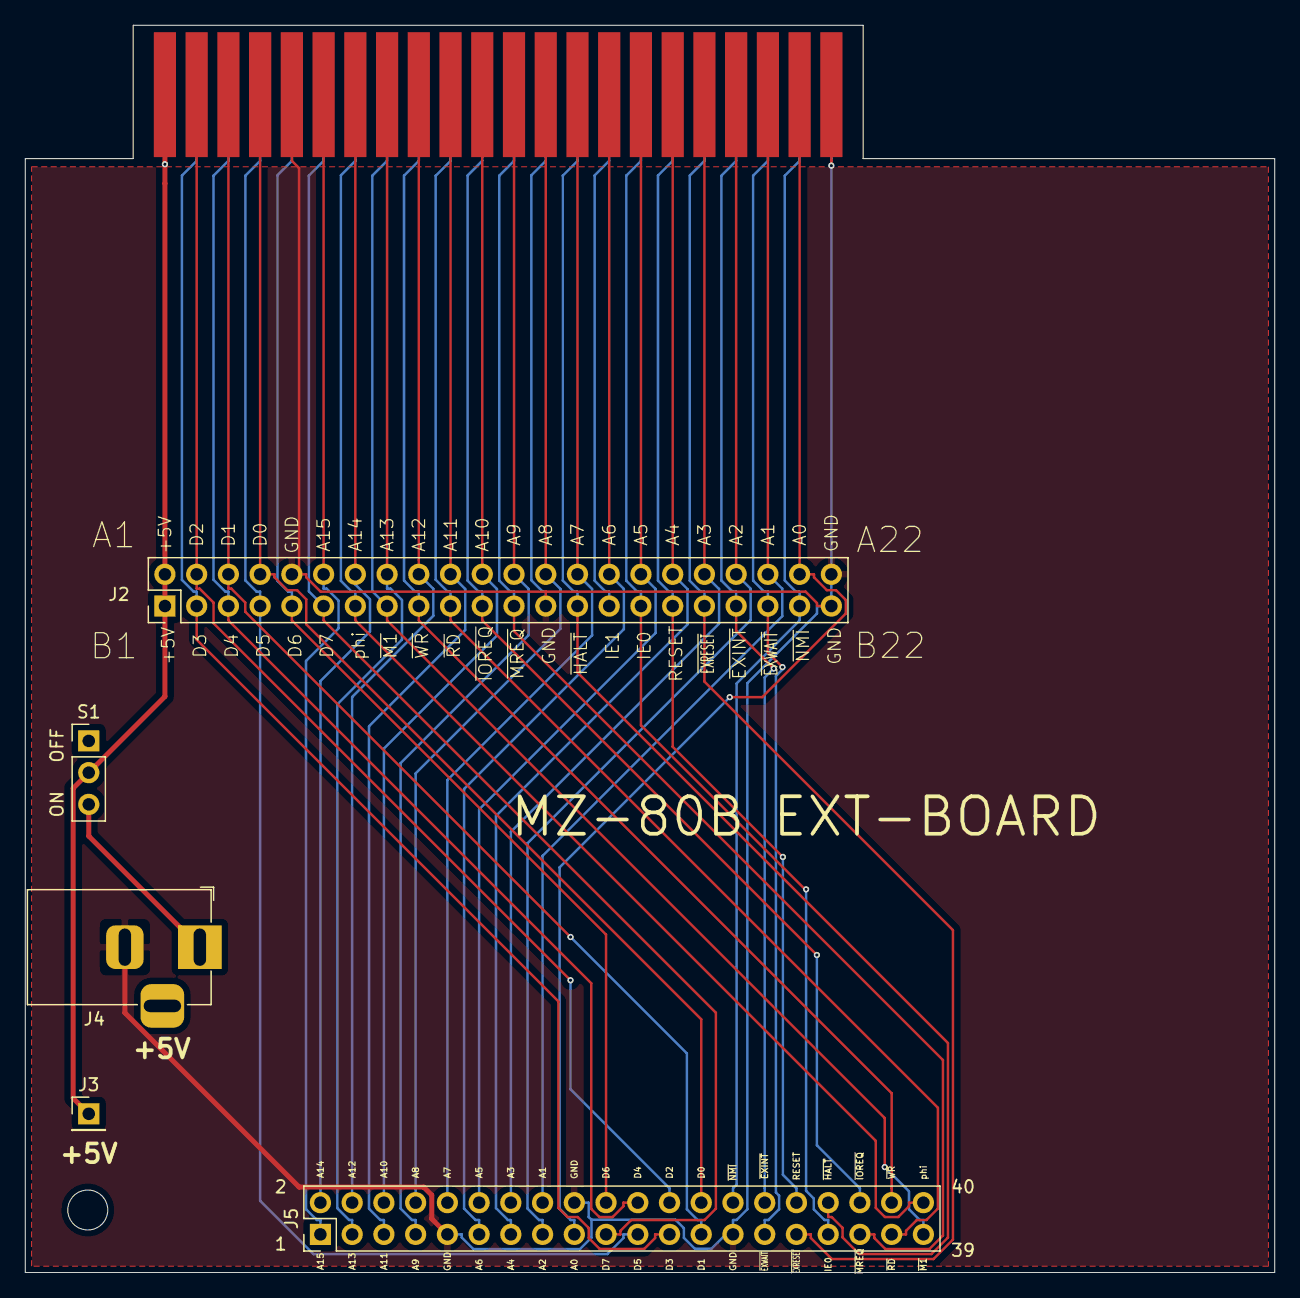
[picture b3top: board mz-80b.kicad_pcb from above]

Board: 2 copper layers, 100.0 x 99.8 mm, 7 parts (0 on the bottom side), 41 nets.

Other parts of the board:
MH1: MountingHole_3.2mm_M3

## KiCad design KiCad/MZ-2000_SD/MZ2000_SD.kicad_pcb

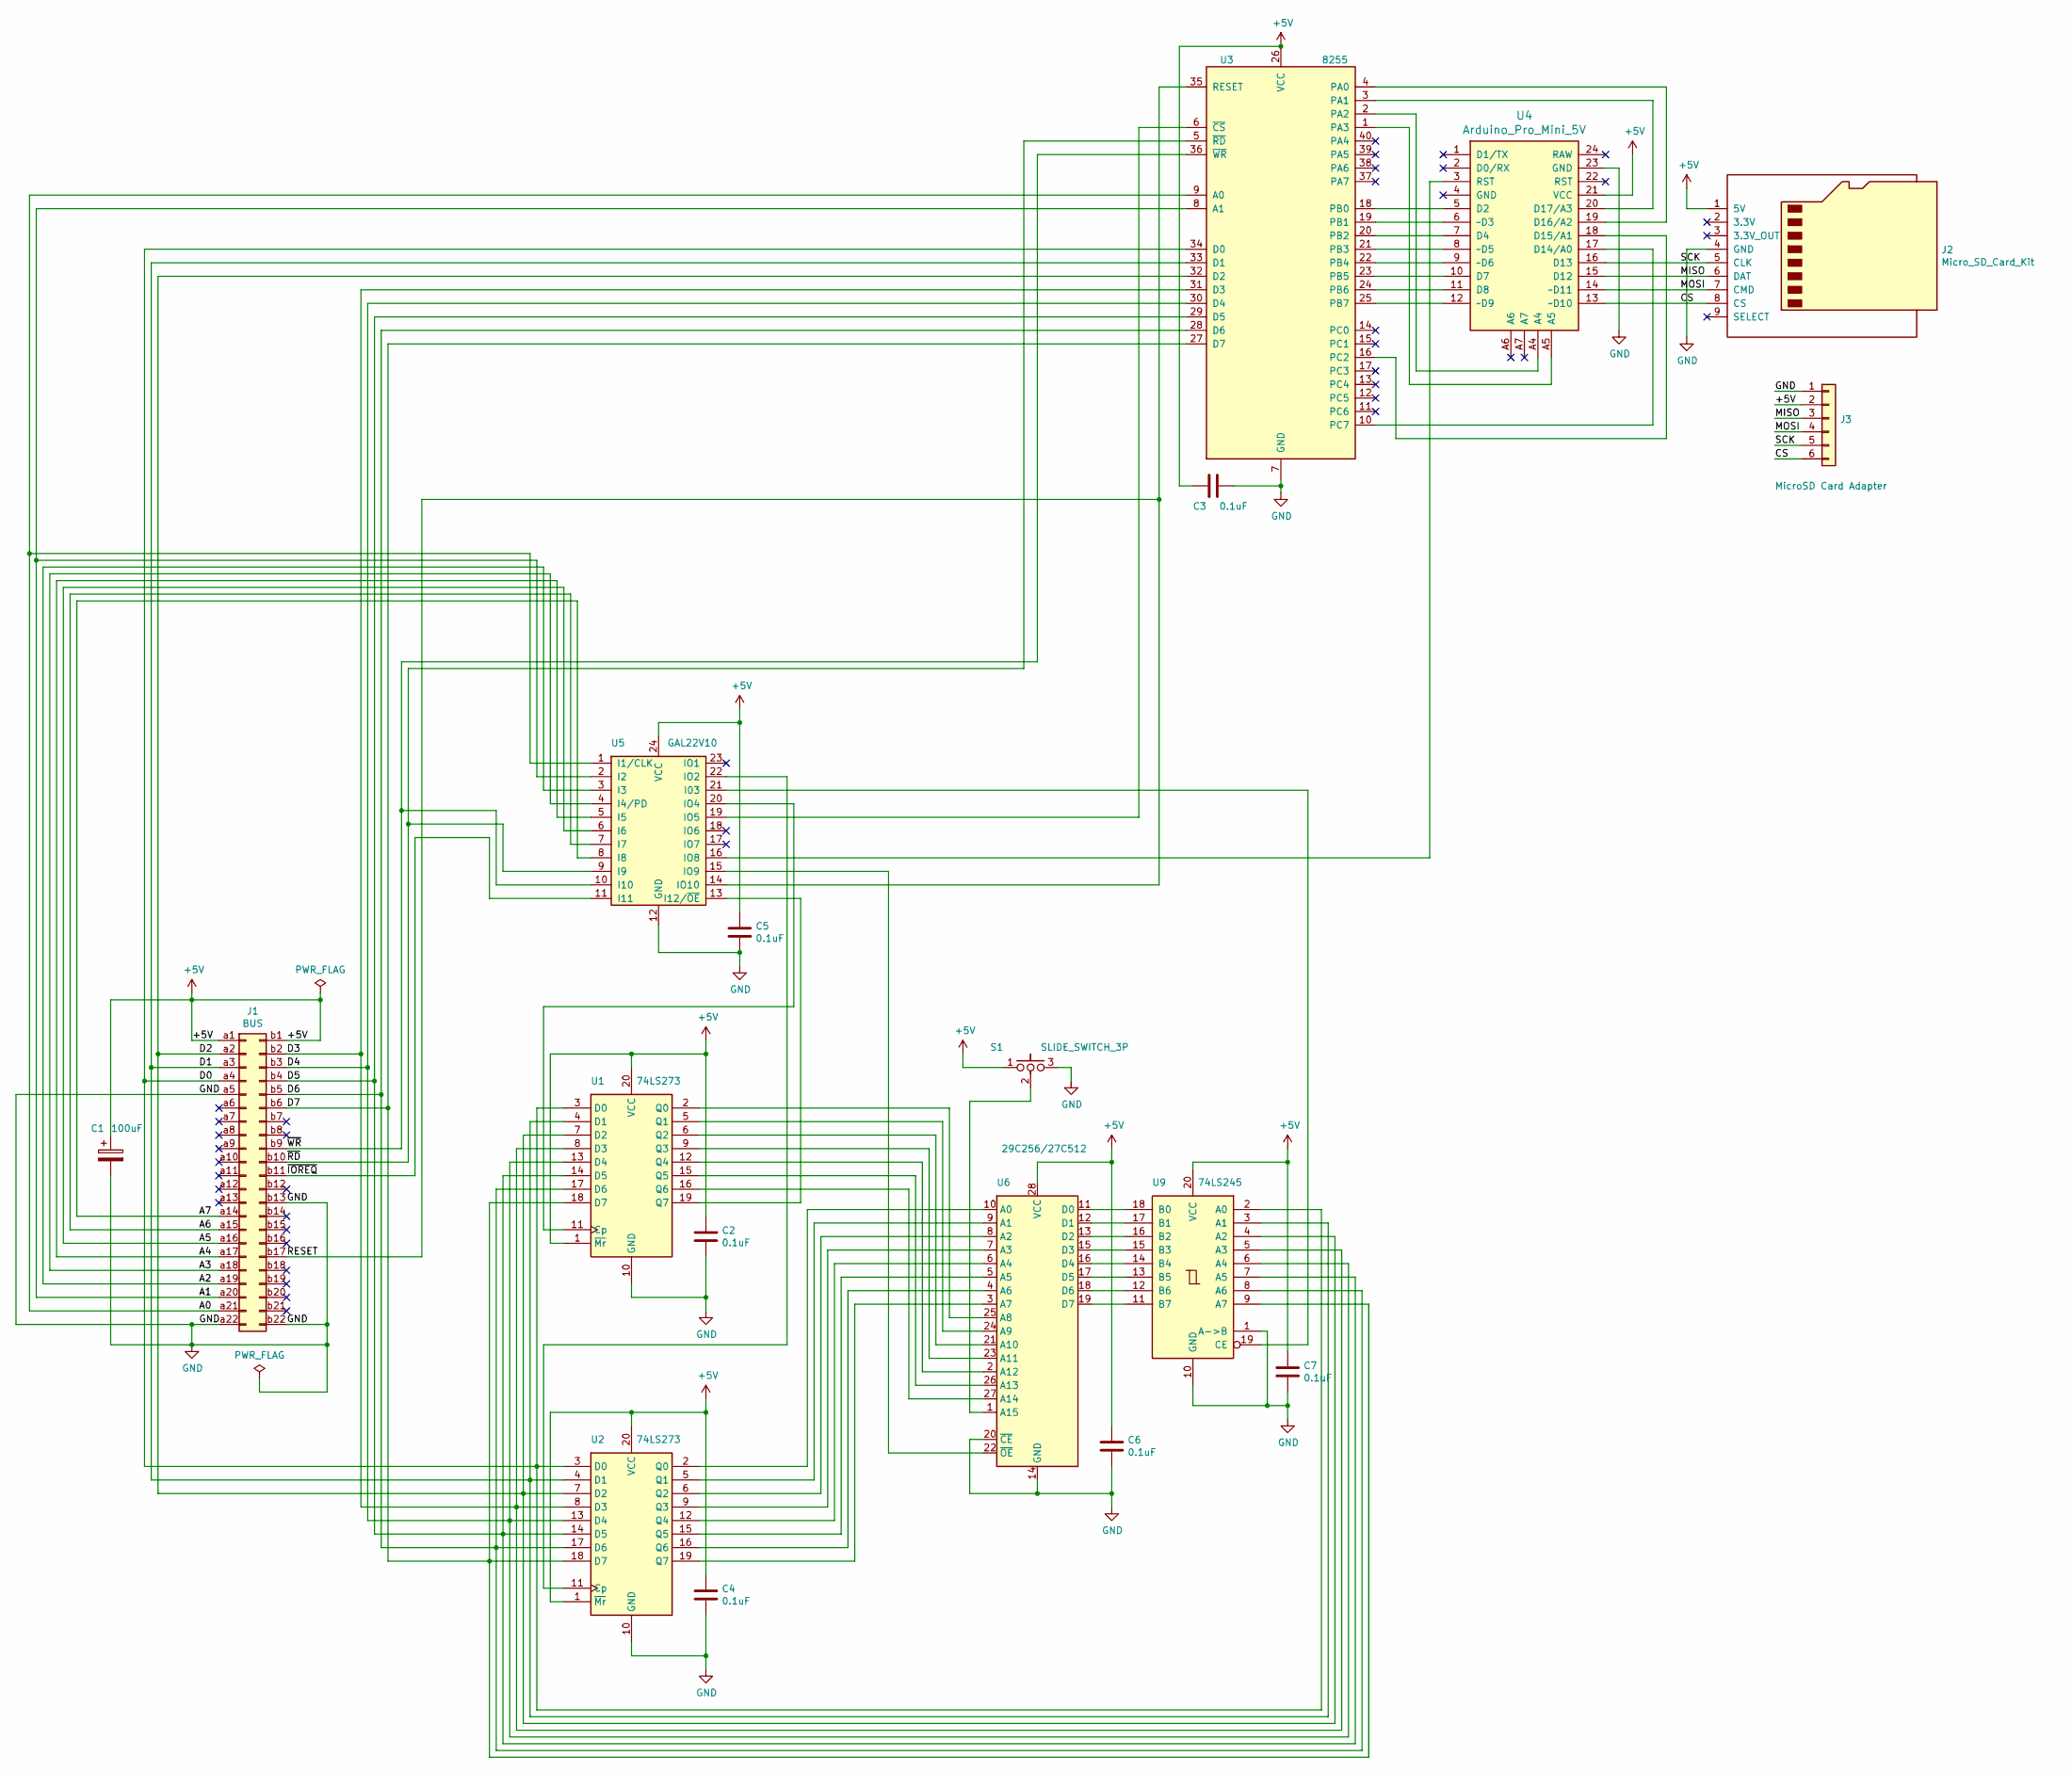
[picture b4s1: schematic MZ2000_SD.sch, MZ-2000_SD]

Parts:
C1: 100uF; CP_Radial_Tantal_D5.0mm_P2.50mm
C2, C3, C4, C5, C6, C7: 0.1uF; C_Rect_L4.0mm_W2.5mm_P2.50mm
J1: BUS; PinHeader_2x22_P2.54mm_Vertical
J2: Micro_SD_Card_Kit; AE-microSD-LLCNV
J3: MicroSD Card Adapter; PinSocket_1x06_P2.54mm_Vertical
S1: SLIDE_SWITCH_3P; PinHeader_1x03_P2.54mm_Vertical
U1, U2: 74LS273; DIP-20_W7.62mm_LongPads
U3: 8255; DIP-40_W15.24mm_LongPads
U4: Arduino_Pro_Mini_5V; Arduino_Pro_Mini
U5: GAL22V10; DIP-24_W7.62mm_LongPads
U6: 29C256/27C512; DIP-28_W15.24mm
U9: 74LS245; DIP-20_W7.62mm_LongPads

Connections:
+5V: C1.1, C2.1, C3.1, C4.1, C5.1, C6.1, C7.1, J1.a1, J1.b1, J2.1 (5V), J3.2, S1.1, U1.1 (~Mr), U1.20 (VCC), U2.1 (~Mr), U2.20 (VCC), U3.26 (VCC), U4.21 (VCC), U5.24 (VCC), U6.28 (VCC), U9.20 (VCC)
/A0: J1.a21, U3.9 (A0), U5.1 (I1/CLK)
/A1: J1.a20, U3.8 (A1), U5.2 (I2)
/A2: J1.a19, U5.3 (I3)
/A3: J1.a18, U5.4 (I4/PD)
/A4: J1.a17, U5.5 (I5)
/A5: J1.a16, U5.6 (I6)
/A6: J1.a15, U5.7 (I7)
/A7: J1.a14, U5.8 (I8)
/CS: J2.8 (CS), J3.6, U4.13 (~~D10)
/D0: J1.a4, U1.3 (D0), U2.3 (D0), U3.34 (D0), U9.2 (A0)
/D1: J1.a3, U1.4 (D1), U2.4 (D1), U3.33 (D1), U9.3 (A1)
/D2: J1.a2, U1.7 (D2), U2.7 (D2), U3.32 (D2), U9.4 (A2)
/D3: J1.b2, U1.8 (D3), U2.8 (D3), U3.31 (D3), U9.5 (A3)
/D4: J1.b3, U1.13 (D4), U2.13 (D4), U3.30 (D4), U9.6 (A4)
/D5: J1.b4, U1.14 (D5), U2.14 (D5), U3.29 (D5), U9.7 (A5)
/D6: J1.b5, U1.17 (D6), U2.17 (D6), U3.28 (D6), U9.8 (A6)
/D7: J1.b6, U1.18 (D7), U2.18 (D7), U3.27 (D7), U9.9 (A7)
/MISO: J2.6 (DAT), J3.3, U4.15 (D12)
/MOSI: J2.7 (CMD), J3.4, U4.14 (~~D11)
/RESET: J1.b17, U3.35 (RESET), U5.14 (IO10)
/SCK: J2.5 (CLK), J3.5, U4.16 (D13)
/~IOREQ: J1.b11, U5.11 (I11)
/~RD: J1.b10, U3.5 (~RD~), U5.9 (I9)
/~WR: J1.b9, U3.36 (~WR~), U5.10 (I10)
GND: C1.2, C2.2, C3.2, C4.2, C5.2, C6.2, C7.2, J1.a5, J1.a22, J1.b13, J1.b22, J2.4 (GND), J3.1, S1.3, U1.10 (GND), U2.10 (GND), U3.7 (GND), U4.23 (GND), U5.12 (GND), U6.14 (GND), U6.20 (~CE), U9.1 (A->B), U9.10 (GND)
unnamed: S1.2, U6.1 (A15)
unnamed: U1.2 (Q0), U6.25 (A8)
unnamed: U1.5 (Q1), U6.24 (A9)
unnamed: U1.6 (Q2), U6.21 (A10)
unnamed: U1.9 (Q3), U6.23 (A11)
unnamed: U1.11 (Cp), U5.20 (IO4)
unnamed: U1.12 (Q4), U6.2 (A12)
unnamed: U1.15 (Q5), U6.26 (A13)
unnamed: U1.16 (Q6), U6.27 (A14)
unnamed: U1.19 (Q7), U5.13 (I12/~OE~)
unnamed: U2.2 (Q0), U6.10 (A0)
unnamed: U2.5 (Q1), U6.9 (A1)
unnamed: U2.6 (Q2), U6.8 (A2)
unnamed: U2.9 (Q3), U6.7 (A3)
unnamed: U2.11 (Cp), U5.22 (IO2)
unnamed: U2.12 (Q4), U6.6 (A4)
unnamed: U2.15 (Q5), U6.5 (A5)
unnamed: U2.16 (Q6), U6.4 (A6)
unnamed: U2.19 (Q7), U6.3 (A7)
unnamed: U3.1 (PA3), U4.A5
unnamed: U3.2 (PA2), U4.A4
unnamed: U3.3 (PA1), U4.20 (D17/A3)
unnamed: U3.4 (PA0), U4.19 (D16/A2)
unnamed: U3.6 (~CS~), U5.19 (IO5)
unnamed: U3.10 (PC7), U4.17 (D14/A0)
unnamed: U3.16 (PC2), U4.18 (D15/A1)
unnamed: U3.18 (PB0), U4.5 (D2)
unnamed: U3.19 (PB1), U4.6 (~~D3)
unnamed: U3.20 (PB2), U4.7 (D4)
unnamed: U3.21 (PB3), U4.8 (~~D5)
unnamed: U3.22 (PB4), U4.9 (~~D6)
unnamed: U3.23 (PB5), U4.10 (D7)
unnamed: U3.24 (PB6), U4.11 (D8)
unnamed: U3.25 (PB7), U4.12 (~~D9)
unnamed: U4.3 (RST), U5.16 (IO8)
unnamed: U5.15 (IO9), U6.22 (~OE)
unnamed: U5.21 (I03), U9.19 (CE)
unnamed: U6.11 (D0), U9.18 (B0)
unnamed: U6.12 (D1), U9.17 (B1)
unnamed: U6.13 (D2), U9.16 (B2)
unnamed: U6.15 (D3), U9.15 (B3)
unnamed: U6.16 (D4), U9.14 (B4)
unnamed: U6.17 (D5), U9.13 (B5)
unnamed: U6.18 (D6), U9.12 (B6)
unnamed: U6.19 (D7), U9.11 (B7)
